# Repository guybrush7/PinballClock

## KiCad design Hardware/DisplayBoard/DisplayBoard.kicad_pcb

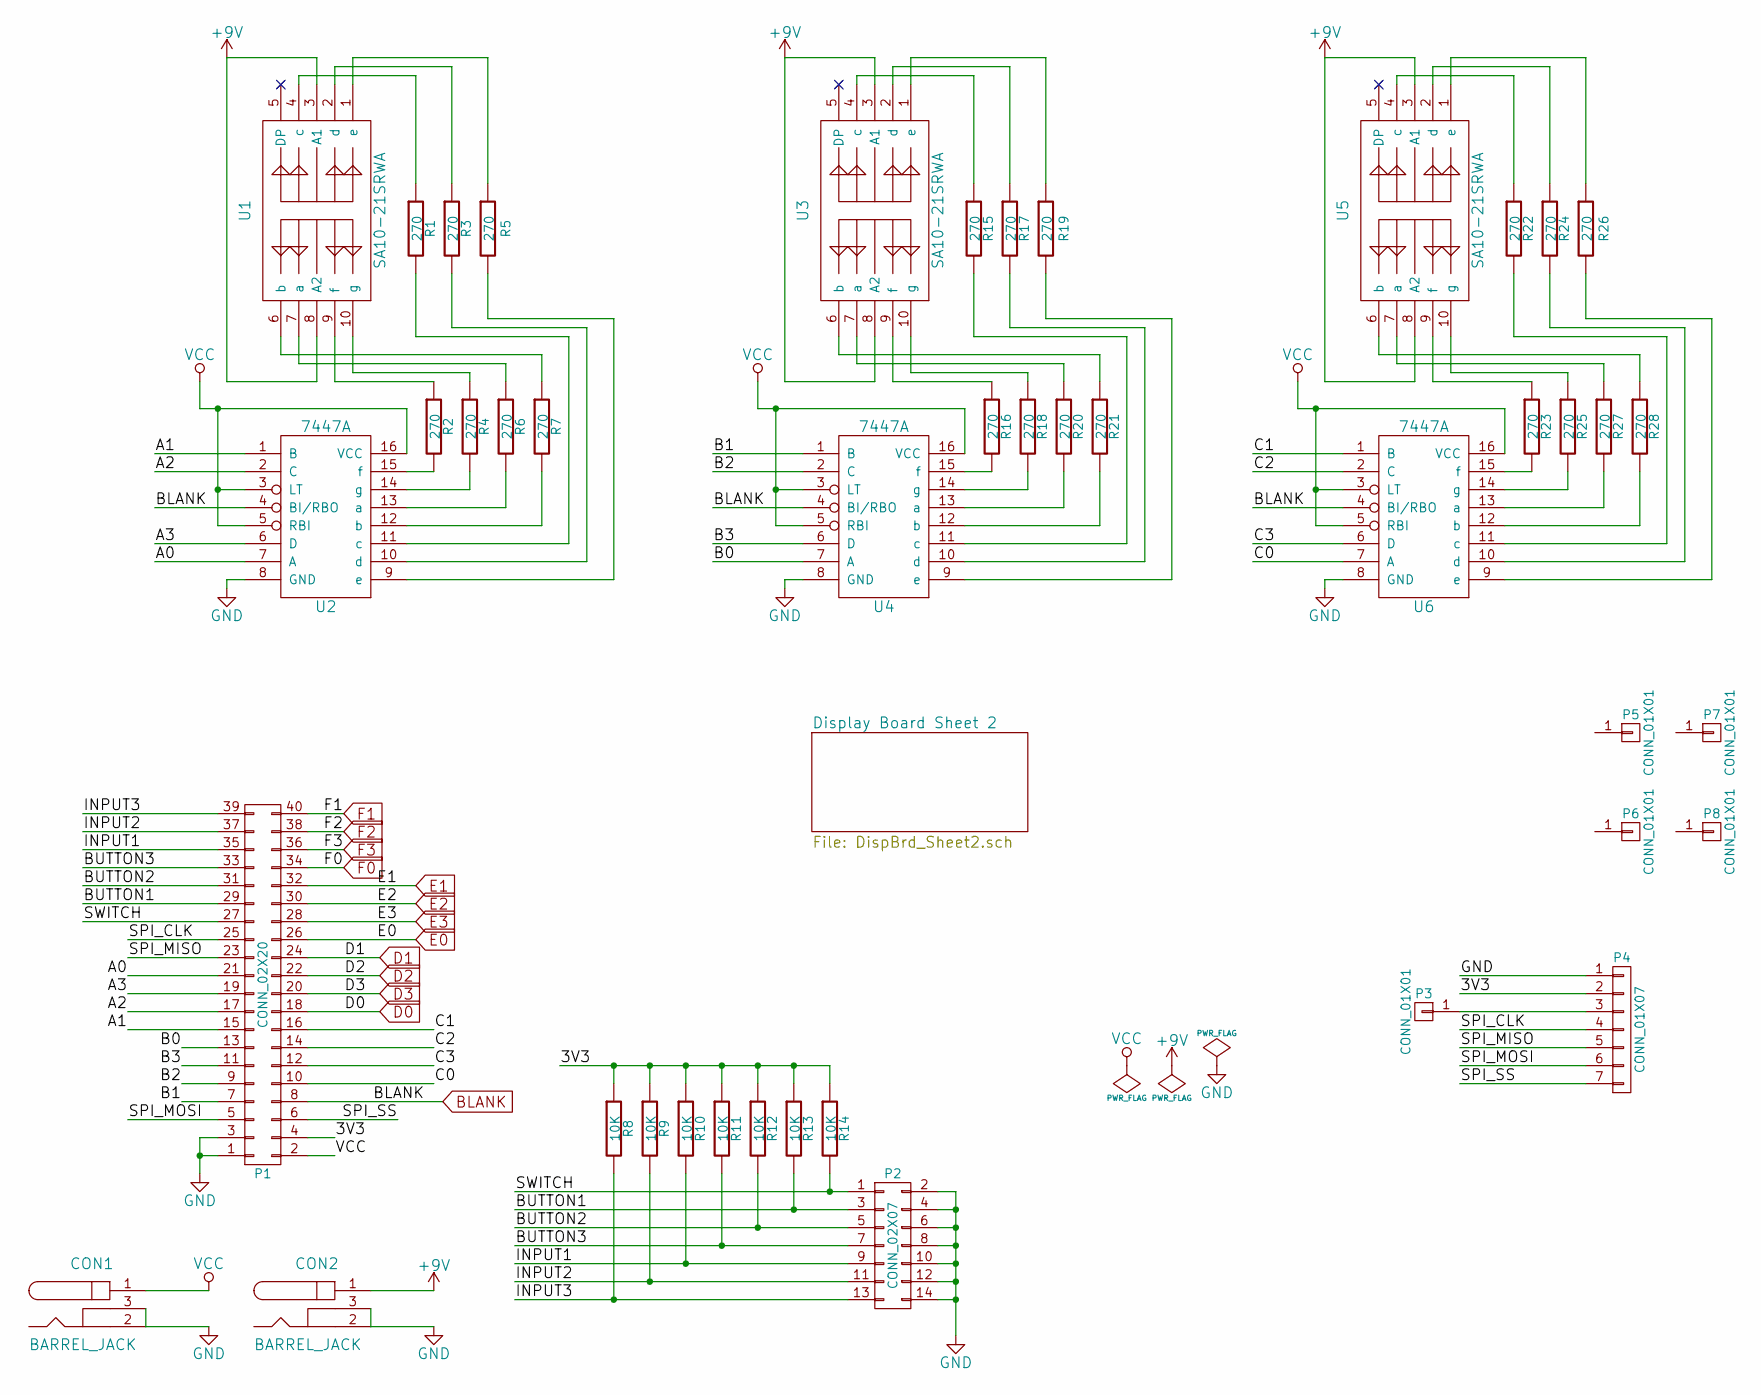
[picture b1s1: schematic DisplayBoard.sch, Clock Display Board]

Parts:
CON1, CON2: BARREL_JACK; Switch_RAPC722X
P1: CONN_02X20; Pin_Header_Straight_2x20
P2: CONN_02X07; Pin_Header_Straight_2x07
P3: CONN_01X01; Pin_Header_Straight_1x01
P4: CONN_01X07; Pin_Header_Straight_1x07
P5, P6, P7, P8: CONN_01X01; Mounting_hole_1-8
R1, R2, R3, R4, R5, R6, R7, R15, R16, R17, R18, R19, R20, R21, R22, R23, R24, R25, R26, R27, R28: 270; R4
R8, R9, R10, R11, R12, R13, R14: 10K; R4
U1, U3, U5: SA10-21SRWA
U2, U4, U6: 7447A; DIP-16__300

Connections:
+9V: CON2.1, U1.3 (A1), U1.8 (A2), U3.3 (A1), U3.8 (A2), U5.3 (A1), U5.8 (A2); also elsewhere on the board
/3V3: P1.4, P4.2, R8.1, R9.1, R10.1, R11.1, R12.1, R13.1, R14.1
/A0: P1.21, U2.7 (A)
/A1: P1.15, U2.1 (B)
/A2: P1.17, U2.2 (C)
/A3: P1.19, U2.6 (D)
/B0: P1.13, U4.7 (A)
/B1: P1.7, U4.1 (B)
/B2: P1.9, U4.2 (C)
/B3: P1.11, U4.6 (D)
/BUTTON1: P1.29, P2.3, R13.2
/BUTTON2: P1.31, P2.5, R12.2
/BUTTON3: P1.33, P2.7, R11.2
/C0: P1.10, U6.7 (A)
/C1: P1.16, U6.1 (B)
/C2: P1.14, U6.2 (C)
/C3: P1.12, U6.6 (D)
/INPUT1: P1.35, P2.9, R10.2
/INPUT2: P1.37, P2.11, R9.2
/INPUT3: P1.39, P2.13, R8.2
/SPI_CLK: P1.25, P4.4
/SPI_MISO: P1.23, P4.5
/SPI_MOSI: P1.5, P4.6
/SPI_SS: P1.6, P4.7
/SWITCH: P1.27, P2.1, R14.2
BLANK: P1.8, U2.4 (BI/RBO), U4.4 (BI/RBO), U6.4 (BI/RBO); also elsewhere on the board
D0: P1.18; also elsewhere on the board
D1: P1.24; also elsewhere on the board
D2: P1.22; also elsewhere on the board
D3: P1.20; also elsewhere on the board
E0: P1.26; also elsewhere on the board
E1: P1.32; also elsewhere on the board
E2: P1.30; also elsewhere on the board
E3: P1.28; also elsewhere on the board
F0: P1.34; also elsewhere on the board
F1: P1.40; also elsewhere on the board
F2: P1.38; also elsewhere on the board
F3: P1.36; also elsewhere on the board
GND: CON1.2, CON1.3, CON2.2, CON2.3, P1.1, P1.3, P2.2, P2.4, P2.6, P2.8, P2.10, P2.12, P2.14, P4.1, U2.8 (GND), U4.8 (GND), U6.8 (GND); also elsewhere on the board
unnamed: P3.1, P4.3
unnamed: R1.1, U1.4 (c)
unnamed: R1.2, U2.11 (c)
unnamed: R2.1, U1.9 (f)
unnamed: R2.2, U2.15 (f)
unnamed: R3.1, U1.2 (d)
unnamed: R3.2, U2.10 (d)
unnamed: R4.1, U1.10 (g)
unnamed: R4.2, U2.14 (g)
unnamed: R5.1, U1.1 (e)
unnamed: R5.2, U2.9 (e)
unnamed: R6.1, U1.7 (a)
unnamed: R6.2, U2.13 (a)
unnamed: R7.1, U1.6 (b)
unnamed: R7.2, U2.12 (b)
unnamed: R15.1, U3.4 (c)
unnamed: R15.2, U4.11 (c)
unnamed: R16.1, U3.9 (f)
unnamed: R16.2, U4.15 (f)
unnamed: R17.1, U3.2 (d)
unnamed: R17.2, U4.10 (d)
unnamed: R18.1, U3.10 (g)
unnamed: R18.2, U4.14 (g)
unnamed: R19.1, U3.1 (e)
unnamed: R19.2, U4.9 (e)
unnamed: R20.1, U3.7 (a)
unnamed: R20.2, U4.13 (a)
unnamed: R21.1, U3.6 (b)
unnamed: R21.2, U4.12 (b)
unnamed: R22.1, U5.4 (c)
unnamed: R22.2, U6.11 (c)
unnamed: R23.1, U5.9 (f)
unnamed: R23.2, U6.15 (f)
unnamed: R24.1, U5.2 (d)
unnamed: R24.2, U6.10 (d)
unnamed: R25.1, U5.10 (g)
unnamed: R25.2, U6.14 (g)
unnamed: R26.1, U5.1 (e)
unnamed: R26.2, U6.9 (e)
unnamed: R27.1, U5.7 (a)
unnamed: R27.2, U6.13 (a)
unnamed: R28.1, U5.6 (b)
unnamed: R28.2, U6.12 (b)
VCC: CON1.1, P1.2, U2.3 (LT), U2.5 (RBI), U2.16 (VCC), U4.3 (LT), U4.5 (RBI), U4.16 (VCC), U6.3 (LT), U6.5 (RBI), U6.16 (VCC); also elsewhere on the board

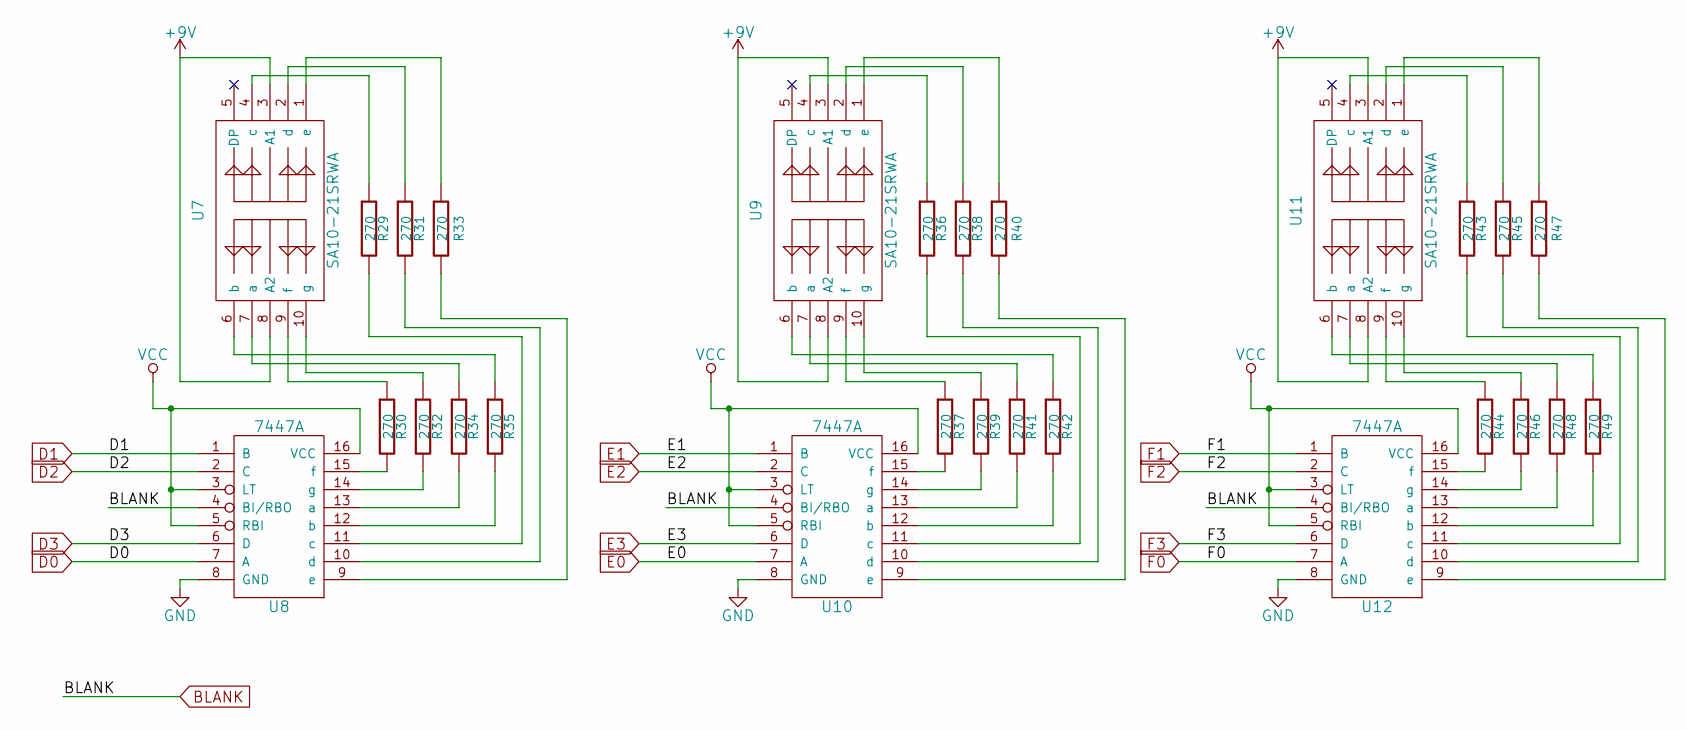
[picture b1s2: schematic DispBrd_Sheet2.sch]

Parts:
R29, R30, R31, R32, R33, R34, R35, R36, R37, R38, R39, R40, R41, R42, R43, R44, R45, R46, R47, R48, R49: 270; R4
U7, U9, U11: SA10-21SRWA
U8, U10, U12: 7447A; DIP-16__300

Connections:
+9V: U7.3 (A1), U7.8 (A2), U9.3 (A1), U9.8 (A2), U11.3 (A1), U11.8 (A2); also elsewhere on the board
BLANK: U8.4 (BI/RBO), U10.4 (BI/RBO), U12.4 (BI/RBO); also elsewhere on the board
D0: U8.7 (A); also elsewhere on the board
D1: U8.1 (B); also elsewhere on the board
D2: U8.2 (C); also elsewhere on the board
D3: U8.6 (D); also elsewhere on the board
E0: U10.7 (A); also elsewhere on the board
E1: U10.1 (B); also elsewhere on the board
E2: U10.2 (C); also elsewhere on the board
E3: U10.6 (D); also elsewhere on the board
F0: U12.7 (A); also elsewhere on the board
F1: U12.1 (B); also elsewhere on the board
F2: U12.2 (C); also elsewhere on the board
F3: U12.6 (D); also elsewhere on the board
GND: U8.8 (GND), U10.8 (GND), U12.8 (GND); also elsewhere on the board
unnamed: R29.1, U7.4 (c)
unnamed: R29.2, U8.11 (c)
unnamed: R30.1, U7.9 (f)
unnamed: R30.2, U8.15 (f)
unnamed: R31.1, U7.2 (d)
unnamed: R31.2, U8.10 (d)
unnamed: R32.1, U7.10 (g)
unnamed: R32.2, U8.14 (g)
unnamed: R33.1, U7.1 (e)
unnamed: R33.2, U8.9 (e)
unnamed: R34.1, U7.7 (a)
unnamed: R34.2, U8.13 (a)
unnamed: R35.1, U7.6 (b)
unnamed: R35.2, U8.12 (b)
unnamed: R36.1, U9.4 (c)
unnamed: R36.2, U10.11 (c)
unnamed: R37.1, U9.9 (f)
unnamed: R37.2, U10.15 (f)
unnamed: R38.1, U9.2 (d)
unnamed: R38.2, U10.10 (d)
unnamed: R39.1, U9.10 (g)
unnamed: R39.2, U10.14 (g)
unnamed: R40.1, U9.1 (e)
unnamed: R40.2, U10.9 (e)
unnamed: R41.1, U9.7 (a)
unnamed: R41.2, U10.13 (a)
unnamed: R42.1, U9.6 (b)
unnamed: R42.2, U10.12 (b)
unnamed: R43.1, U11.4 (c)
unnamed: R43.2, U12.11 (c)
unnamed: R44.1, U11.9 (f)
unnamed: R44.2, U12.15 (f)
unnamed: R45.1, U11.2 (d)
unnamed: R45.2, U12.10 (d)
unnamed: R46.1, U11.10 (g)
unnamed: R46.2, U12.14 (g)
unnamed: R47.1, U11.1 (e)
unnamed: R47.2, U12.9 (e)
unnamed: R48.1, U11.7 (a)
unnamed: R48.2, U12.13 (a)
unnamed: R49.1, U11.6 (b)
unnamed: R49.2, U12.12 (b)
VCC: U8.3 (LT), U8.5 (RBI), U8.16 (VCC), U10.3 (LT), U10.5 (RBI), U10.16 (VCC), U12.3 (LT), U12.5 (RBI), U12.16 (VCC); also elsewhere on the board

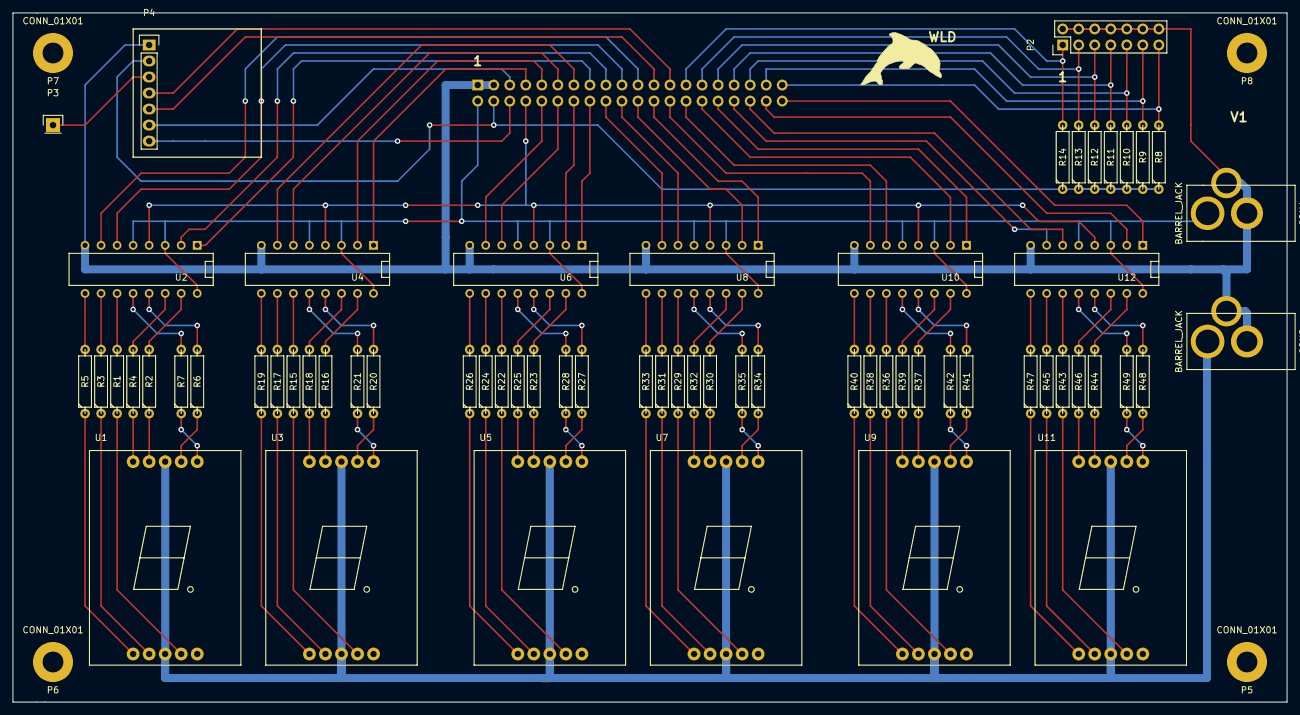
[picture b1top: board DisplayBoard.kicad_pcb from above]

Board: 2 copper layers, 201.9 x 109.2 mm, 71 parts (1 on the bottom side), 125 nets.

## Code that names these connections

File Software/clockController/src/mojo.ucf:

#Created by Constraints Editor (xc6slx9-tqg144-3) - 2012/11/05
NET "clk" TNM_NET = clk;
TIMESPEC TS_clk = PERIOD "clk" 50 MHz HIGH 50%;

# PlanAhead Generated physical constraints 
NET "clk" LOC = P56;
NET "rst_n" LOC = P38;

NET "cclk" LOC = P70;

NET "led<0>" LOC = P134;
NET "led<1>" LOC = P133;
NET "led<2>" LOC = P132;
NET "led<3>" LOC = P131;
NET "led<4>" LOC = P127;
NET "led<5>" LOC = P126;
NET "led<6>" LOC = P124;
NET "led<7>" LOC = P123;

NET "spi_mosi" LOC = P44;
NET "spi_miso" LOC = P45;
NET "spi_ss" LOC = P48;
NET "spi_sck" LOC = P43;
NET "spi_channel<0>" LOC = P46;
NET "spi_channel<1>" LOC = P61;
NET "spi_channel<2>" LOC = P62;
NET "spi_channel<3>" LOC = P65;

NET "avr_tx" LOC = P55;
NET "avr_rx" LOC = P59;
NET "avr_rx_busy" LOC = P39;


NET "L64P_0" LOC = P117;
NET "L65P_0" LOC = P115;
NET "L66P_0" LOC = P112;
NET "L1P_1" LOC = P105;
NET "L32P_1" LOC = P102;
NET "L33P_1" LOC = P100;
NET "L34P_1" LOC = P98;
NET "L40P_1" LOC = P95;
NET "L41P_1" LOC = P93;
NET "L42P_1" LOC = P88;
NET "L43P_1" LOC = P85;
NET "L45P_1" LOC = P83;
NET "L46P_1" LOC = P81;
NET "L47P_1" LOC = P79;
NET "L74P_1" LOC = P75;
NET "L2P_2" LOC = P67;
NET "L14P_2" LOC = P58;
		
NET "L64N_0" LOC = P116;
NET "L65N_0" LOC = P114;
NET "L66N_0" LOC = P111;
NET "L1N_1" LOC = P104;
NET "L32N_1" LOC = P101;
NET "L33N_1" LOC = P99;
NET "L34N_1" LOC = P97;
NET "L40N_1" LOC = P94;
NET "L41N_1" LOC = P92;
NET "L42N_1" LOC = P87;
NET "L43N_1" LOC = P84;
NET "L45N_1" LOC = P82;
NET "L46N_1" LOC = P80;
NET "L47N_1" LOC = P78;
NET "L74N_1" LOC = P74;
NET "L2N_2" LOC = P66;
NET "L14N_2" LOC = P57;
		
NET "L3P_0" LOC = P140;
NET "L2P_0" LOC = P142;
NET "L1P_0" LOC = P144;
NET "L83P_3" LOC = P2;
NET "L52P_3" LOC = P6;
NET "L51P_3" LOC = P8;
NET "L50P_3" LOC = P10;
NET "L49P_3" LOC = P12;
NET "L44P_3" LOC = P15;
NET "L43P_3" LOC = P17;
NET "L42P_3" LOC = P22;
NET "L41P_3" LOC = P24;
NET "L37P_3" LOC = P27;
NET "L36P_3" LOC = P30;
NET "L2P_3" LOC = P33;
NET "L1P_3" LOC = P35;
NET "L64P_2" LOC = P41;
NET "L31P_2" LOC = P51;
		
NET "L3N_0" LOC = P139;
NET "L2N_0" LOC = P141;
NET "L1N_0" LOC = P143;
NET "L83N_3" LOC = P1;
NET "L52N_3" LOC = P5;
NET "L51N_3" LOC = P7;
NET "L50N_3" LOC = P9;
NET "L49N_3" LOC = P11;
NET "L44N_3" LOC = P14;
NET "L43N_3" LOC = P16;
NET "L42N_3" LOC = P21;
NET "L41N_3" LOC = P23;
NET "L37N_3" LOC = P26;
NET "L36N_3" LOC = P29;
NET "L2N_3" LOC = P32;
NET "L1N_3" LOC = P34;
NET "L64N_2" LOC = P40;
NET "L31N_2" LOC = P50;

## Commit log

2016-09-10 :neckbeard: Added .gitattributes
2016-09-10 initial git version
2016-09-10 initial
    keeps time in rtc
2016-09-10 reorg
2016-09-10 v1 commit
2016-09-11 Added date
    Complete. Synthesized but not tested.
